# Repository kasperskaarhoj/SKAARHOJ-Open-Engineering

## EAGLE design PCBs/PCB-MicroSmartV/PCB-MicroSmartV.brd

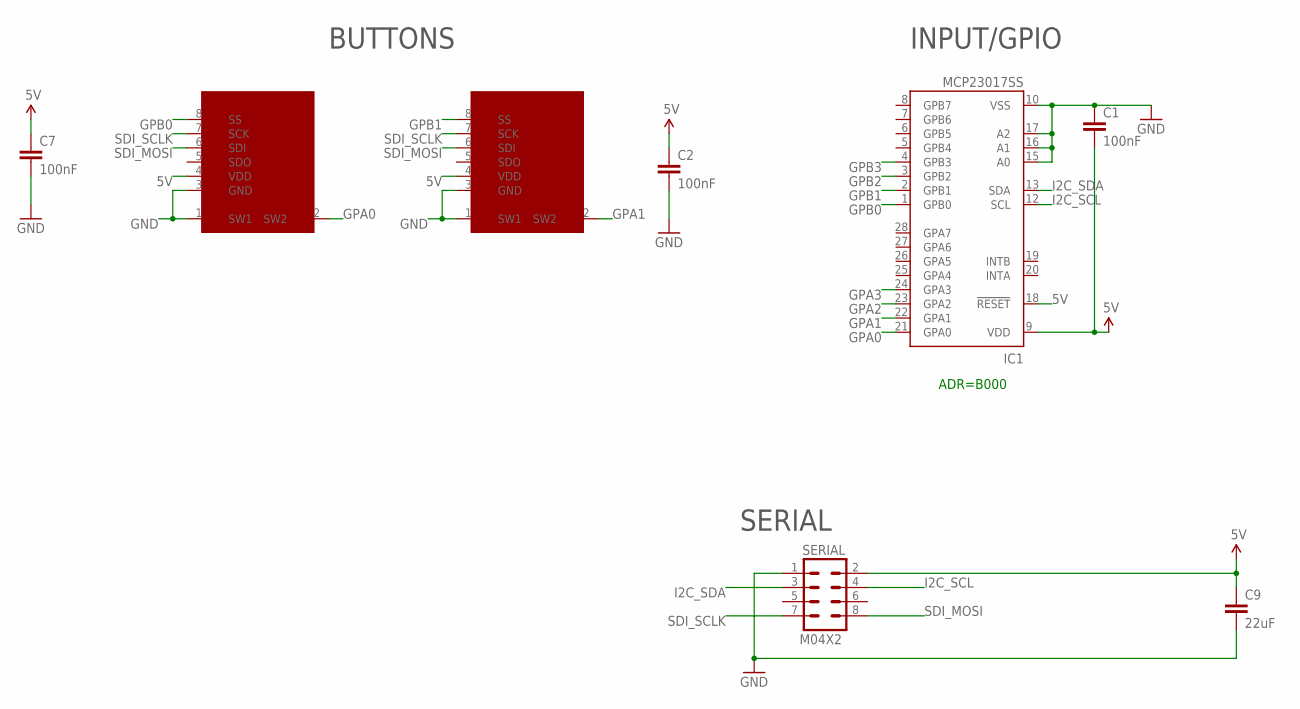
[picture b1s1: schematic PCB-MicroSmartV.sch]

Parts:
C1, C2, C7: 100nF; 0603-CAP
C9: 22uF; 0805
IC1: MCP23017SS; SSOP28; MPN MCP23017-E/SS
SERIAL: M04X2; 2X4
SSW1, SSW2: SMART_SWITCHSMART_SWITCH_8PIN; SMART_SWITCH

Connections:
5V: C1.2, C2.1, C7.1, C9.1, IC1.9 (VDD), IC1.18 (!RESET), SERIAL.2, SSW1.4 (VDD), SSW2.4 (VDD)
GND: C1.1, C2.2, C7.2, C9.2, IC1.10 (VSS), IC1.15 (A0), IC1.16 (A1), IC1.17 (A2), SERIAL.1, SSW1.1 (SW1), SSW1.3 (GND), SSW2.1 (SW1), SSW2.3 (GND)
GPA0: IC1.21 (GPA0), SSW1.2 (SW2)
GPA1: IC1.22 (GPA1), SSW2.2 (SW2)
GPA2: IC1.23 (GPA2)
GPA3: IC1.24 (GPA3)
GPB0: IC1.1 (GPB0), SSW1.8 (SS)
GPB1: IC1.2 (GPB1), SSW2.8 (SS)
GPB2: IC1.3 (GPB2)
GPB3: IC1.4 (GPB3)
I2C_SCL: IC1.12 (SCL), SERIAL.4
I2C_SDA: IC1.13 (SDA), SERIAL.3
SDI_MOSI: SERIAL.8, SSW1.6 (SDI), SSW2.6 (SDI)
SDI_SCLK: SERIAL.7, SSW1.7 (SCK), SSW2.7 (SCK)

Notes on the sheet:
ADR=B000
INPUT/GPIO
SERIAL
BUTTONS

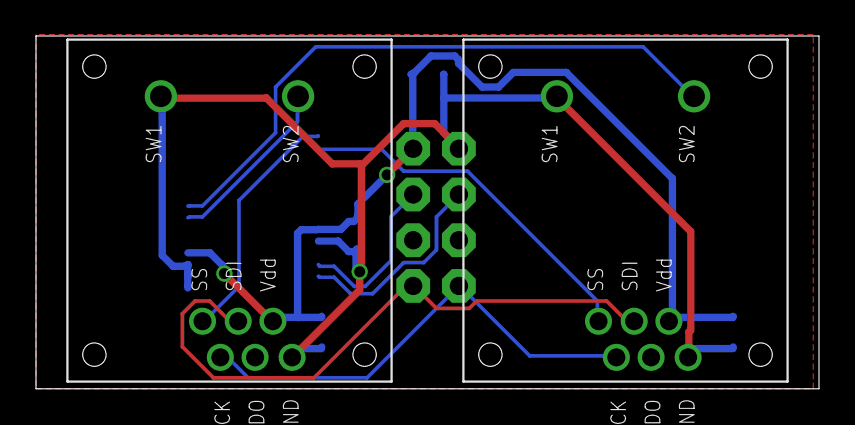
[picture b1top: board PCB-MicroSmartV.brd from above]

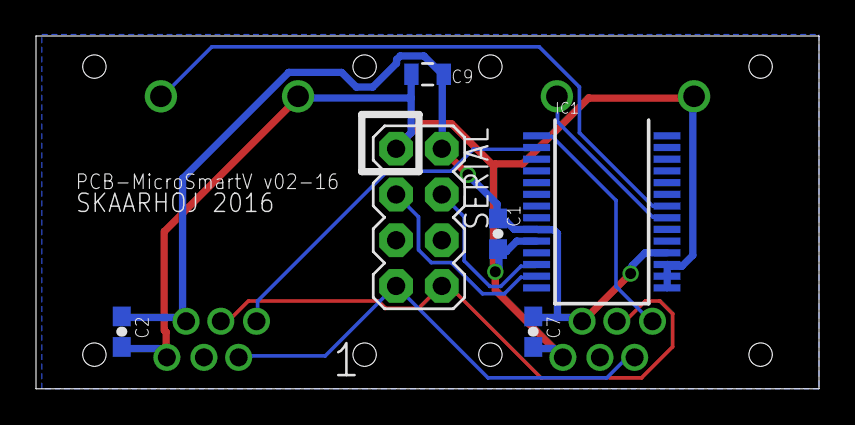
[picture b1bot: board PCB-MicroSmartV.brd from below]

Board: 2 copper layers, 43.5 x 19.6 mm, 8 parts (6 on the bottom side), 10 nets.

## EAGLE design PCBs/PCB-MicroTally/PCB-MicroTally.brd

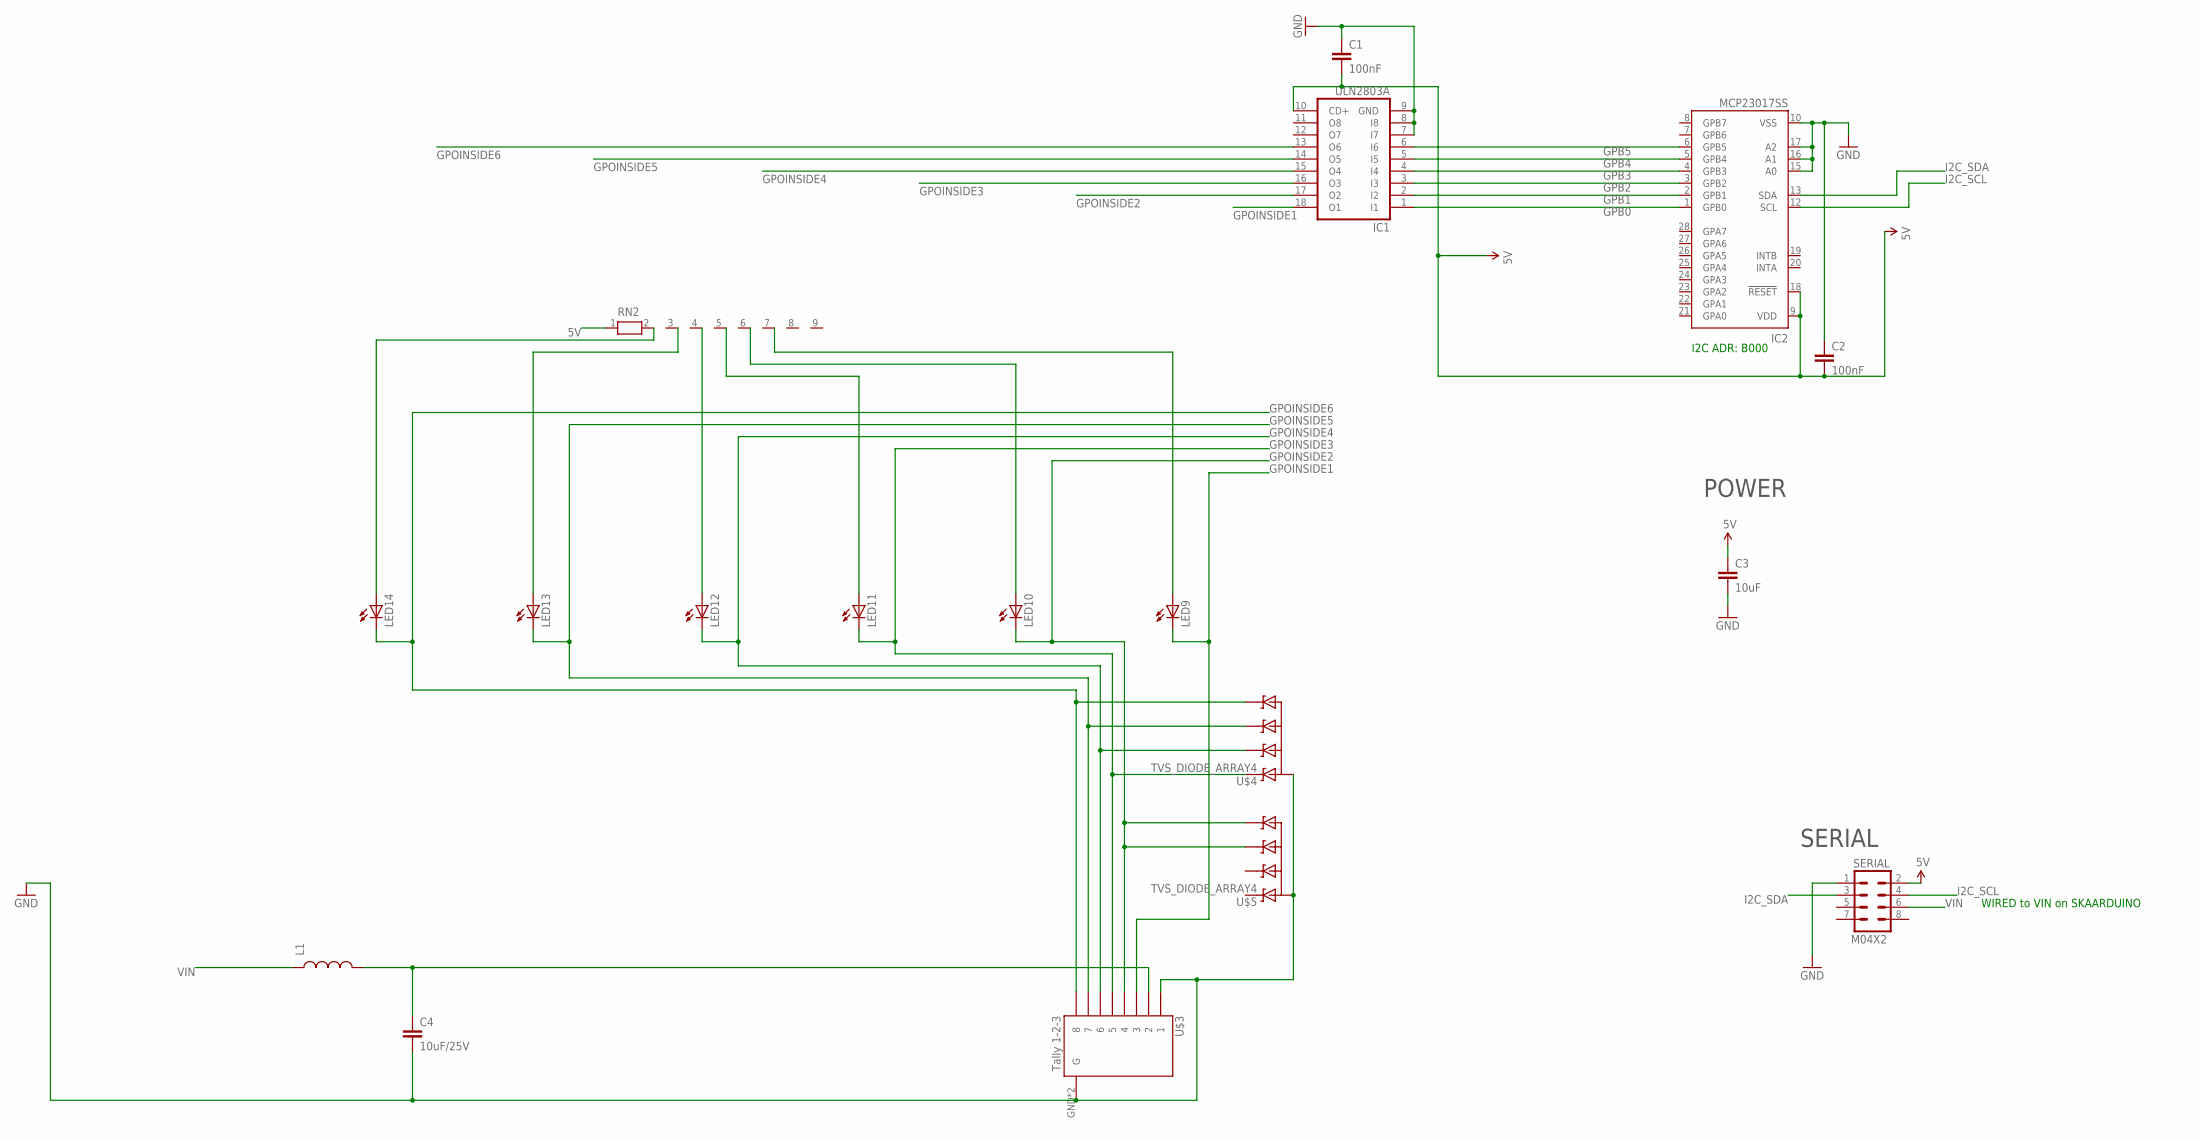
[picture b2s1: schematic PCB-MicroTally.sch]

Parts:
C1: 100nF; 0805
C2: 100nF; 0603-CAP
C3: 10uF; 0805
C4: 10uF/25V; 0805
IC1: ULN2803A; SO18W
IC2: MCP23017SS; SSOP28
L1: INDUCTOR0805; 0805
LED9, LED10, LED11, LED12, LED13, LED14: LED3MM
RN2: RN08; RN-9
SERIAL: M04X2; 2X4
U$3: Tally 1-2-3; RJ45-8_GND_UPRIGHT
U$4, U$5: TVS_DIODE_ARRAY4; SOT23-6L

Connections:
5V: C1.2, C2.2, C3.1, IC1.10 (CD+), IC2.9 (VDD), IC2.18 (!RESET), RN2.1, SERIAL.2
GND: C1.1, C2.1, C3.2, C4.2, IC1.7 (I7), IC1.8 (I8), IC1.9 (GND), IC2.10 (VSS), IC2.15 (A0), IC2.16 (A1), IC2.17 (A2), SERIAL.1, U$3.1, U$3.GND (G), U$3.GND1 (G), U$4.2 (GND), U$4.5 (GND), U$5.2 (GND), U$5.5 (GND)
GPB0: IC1.1 (I1), IC2.1 (GPB0)
GPB1: IC1.2 (I2), IC2.2 (GPB1)
GPB2: IC1.3 (I3), IC2.3 (GPB2)
GPB3: IC1.4 (I4), IC2.4 (GPB3)
GPB4: IC1.5 (I5), IC2.5 (GPB4)
GPB5: IC1.6 (I6), IC2.6 (GPB5)
GPOINSIDE1: IC1.18 (O1), LED9.K (C), U$3.3
GPOINSIDE2: IC1.17 (O2), LED10.K (C), U$3.4, U$5.4 (C), U$5.6 (D)
GPOINSIDE3: IC1.16 (O3), LED11.K (C), U$3.5, U$4.1 (A)
GPOINSIDE4: IC1.15 (O4), LED12.K (C), U$3.6, U$4.3 (B)
GPOINSIDE5: IC1.14 (O5), LED13.K (C), U$3.7, U$4.4 (C)
GPOINSIDE6: IC1.13 (O6), LED14.K (C), U$3.8, U$4.6 (D)
I2C_SCL: IC2.12 (SCL), SERIAL.4
I2C_SDA: IC2.13 (SDA), SERIAL.3
unnamed: C4.1, L1.2, U$3.2
unnamed: LED14.A, RN2.2
unnamed: LED13.A, RN2.3
unnamed: LED12.A, RN2.4
unnamed: LED11.A, RN2.5
unnamed: LED10.A, RN2.6
unnamed: LED9.A, RN2.7
VIN: L1.1, SERIAL.6

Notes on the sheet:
I2C ADR: B000
SERIAL
POWER
WIRED to VIN on SKAARDUINO

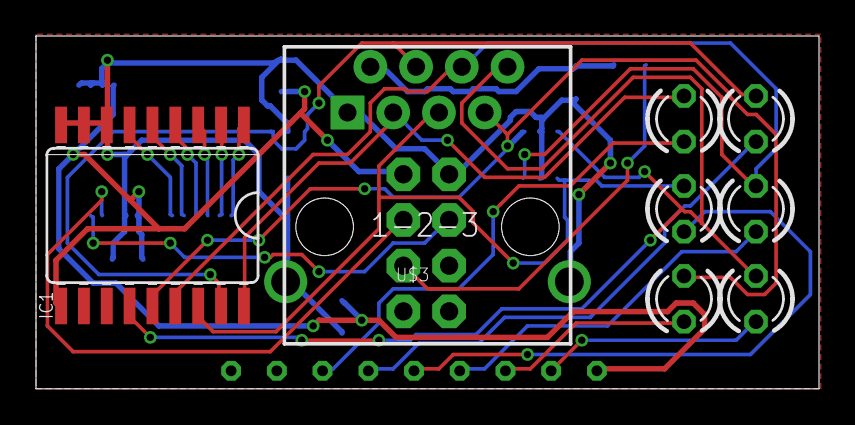
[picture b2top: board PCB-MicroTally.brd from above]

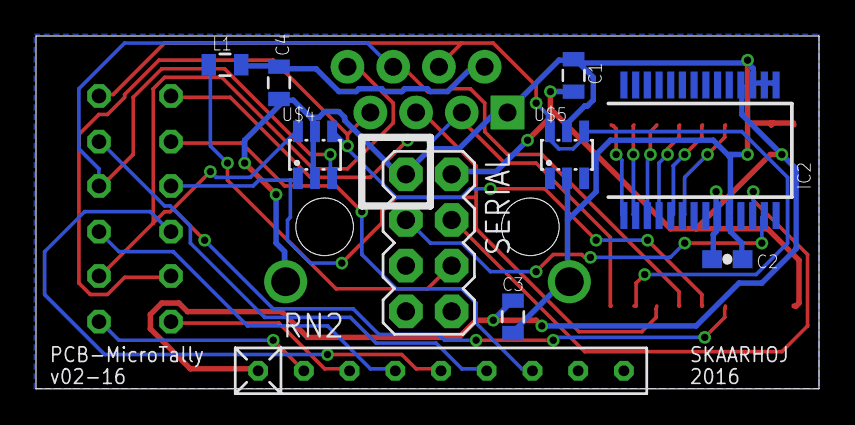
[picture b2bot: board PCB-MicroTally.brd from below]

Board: 2 copper layers, 43.5 x 19.6 mm, 18 parts (10 on the bottom side), 24 nets.

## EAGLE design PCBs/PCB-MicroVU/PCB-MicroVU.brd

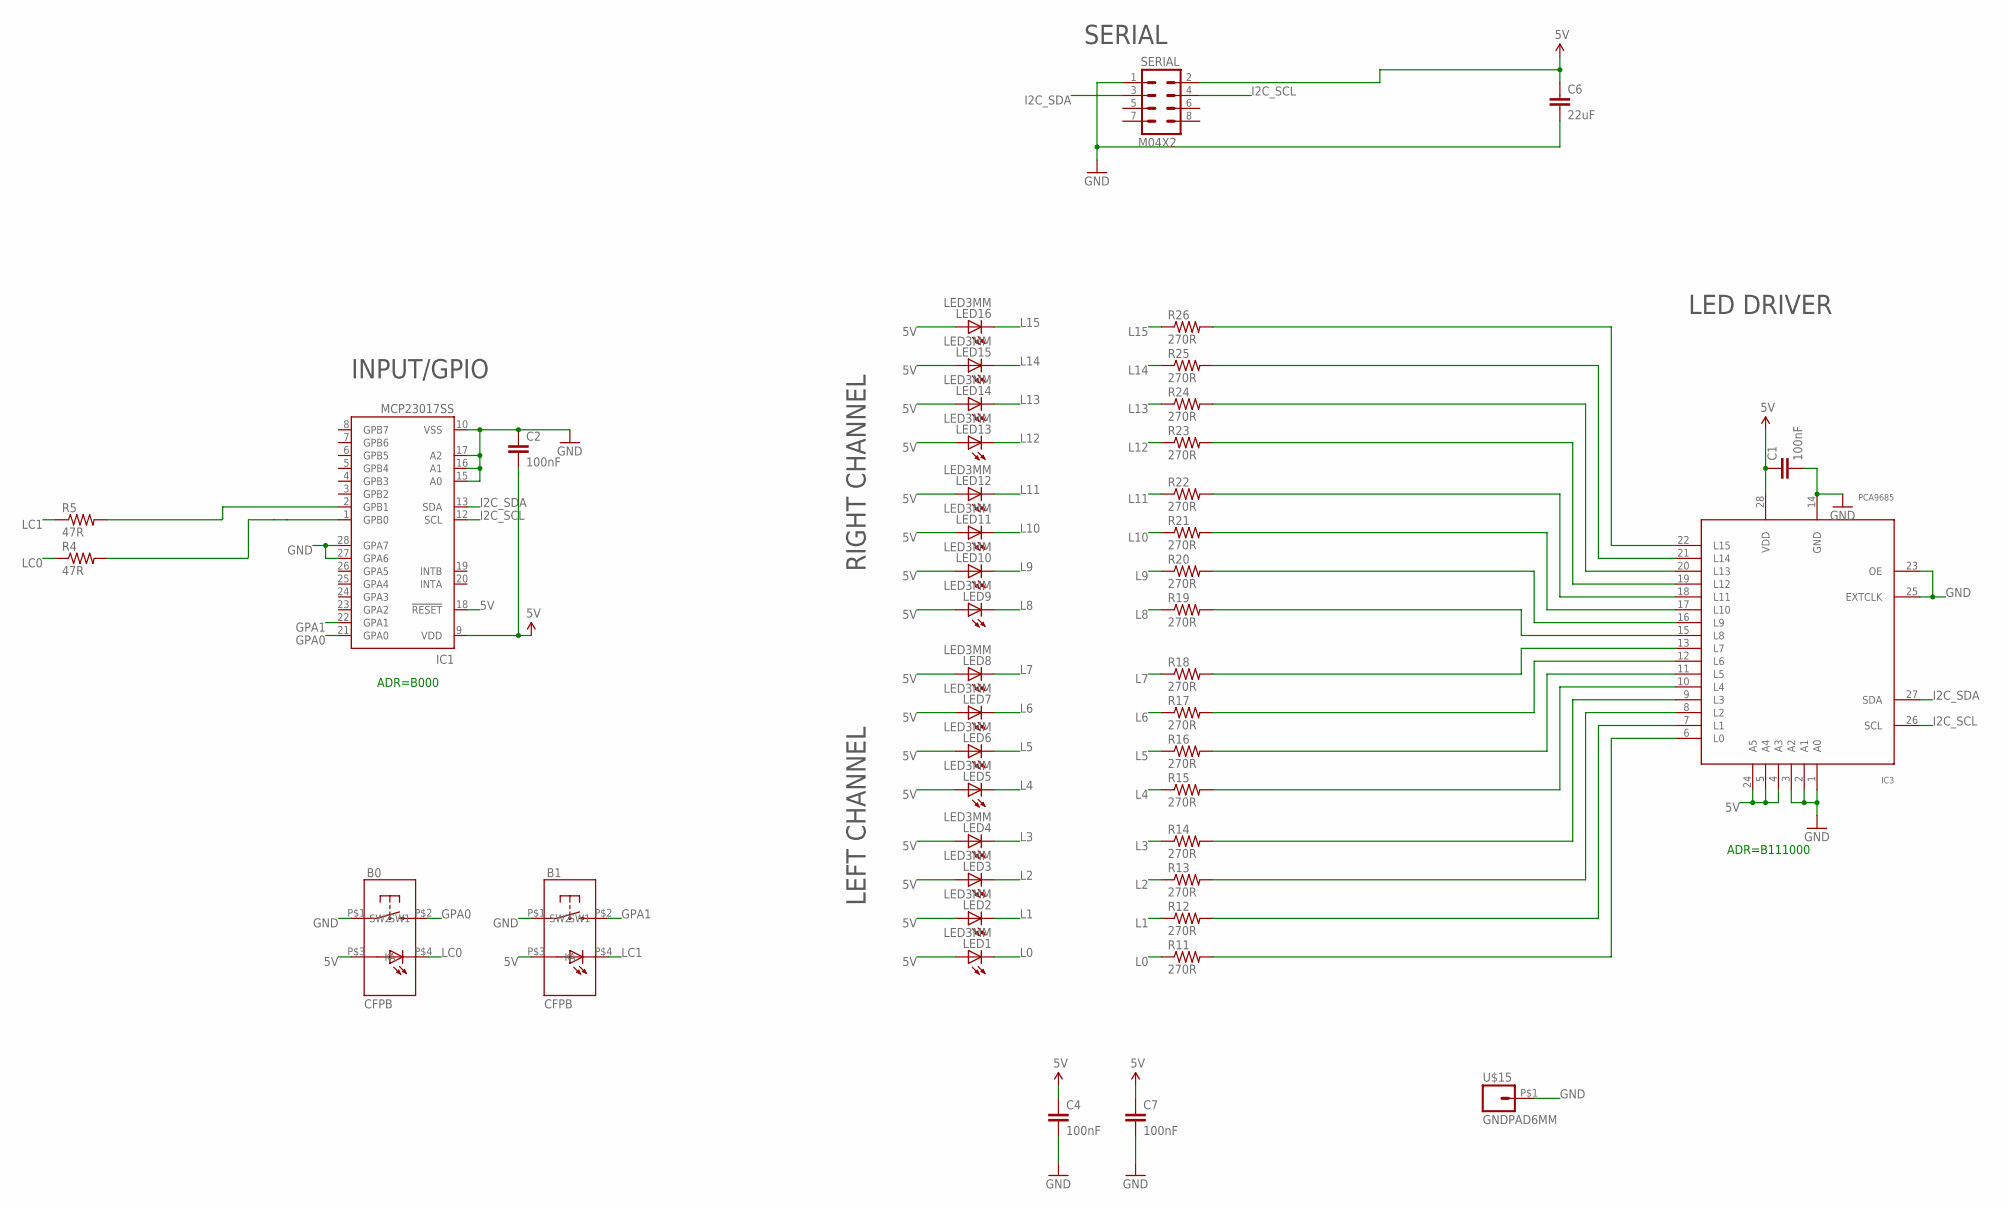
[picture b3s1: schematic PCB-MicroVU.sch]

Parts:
B0, B1: CFPB; CFPB-6/9MM
C1, C2, C4, C7: 100nF; 0603-CAP
C6: 22uF; 0805
IC1: MCP23017SS; SSOP28; MPN MCP23017-E/SS
IC3: PCA9685; TSSOP28
LED1, LED2, LED3, LED4, LED5, LED6, LED7, LED8, LED9, LED10, LED11, LED12, LED13, LED14, LED15, LED16: LED3MM
R4, R5: 47R; 0603-RES
R11, R12, R13, R14, R15, R16, R17, R18, R19, R20, R21, R22, R23, R24, R25, R26: 270R; 0603-RES
SERIAL: M04X2; 2X4
U$15: GNDPAD6MM; 3.2MMPAD6MM

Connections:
5V: B0.P$3 (A), B1.P$3 (A), C1.1, C2.2, C4.1, C6.1, C7.1, IC1.9 (VDD), IC1.18 (!RESET), IC3.4 (A3), IC3.5 (A4), IC3.24 (A5), IC3.28 (VDD), LED1.A, LED2.A, LED3.A, LED4.A, LED5.A, LED6.A, LED7.A, LED8.A, LED9.A, LED10.A, LED11.A, LED12.A, LED13.A, LED14.A, LED15.A, LED16.A, SERIAL.2
GND: B0.P$1 (SW1), B1.P$1 (SW1), C1.2, C2.1, C4.2, C6.2, C7.2, IC1.10 (VSS), IC1.15 (A0), IC1.16 (A1), IC1.17 (A2), IC1.27 (GPA6), IC1.28 (GPA7), IC3.1 (A0), IC3.2 (A1), IC3.3 (A2), IC3.14 (GND), IC3.23 (OE), IC3.25 (EXTCLK), SERIAL.1, U$15.P$1
GPA0: B0.P$2 (SW2), IC1.21 (GPA0)
GPA1: B1.P$2 (SW2), IC1.22 (GPA1)
I2C_SCL: IC1.12 (SCL), IC3.26 (SCL), SERIAL.4
I2C_SDA: IC1.13 (SDA), IC3.27 (SDA), SERIAL.3
L0: LED1.K (C), R11.1
L1: LED2.K (C), R12.1
L2: LED3.K (C), R13.1
L3: LED4.K (C), R14.1
L4: LED5.K (C), R15.1
L5: LED6.K (C), R16.1
L6: LED7.K (C), R17.1
L7: LED8.K (C), R18.1
L8: LED9.K (C), R19.1
L9: LED10.K (C), R20.1
L10: LED11.K (C), R21.1
L11: LED12.K (C), R22.1
L12: LED13.K (C), R23.1
L13: LED14.K (C), R24.1
L14: LED15.K (C), R25.1
L15: LED16.K (C), R26.1
LC0: B0.P$4 (K), R4.1
LC1: B1.P$4 (K), R5.1
unnamed: IC1.2 (GPB1), R5.2
unnamed: IC1.1 (GPB0), R4.2
unnamed: IC3.6 (L0), R11.2
unnamed: IC3.19 (L12), R23.2
unnamed: IC3.21 (L14), R25.2
unnamed: IC3.13 (L7), R18.2
unnamed: IC3.12 (L6), R17.2
unnamed: IC3.11 (L5), R16.2
unnamed: IC3.10 (L4), R15.2
unnamed: IC3.9 (L3), R14.2
unnamed: IC3.8 (L2), R13.2
unnamed: IC3.7 (L1), R12.2
unnamed: IC3.15 (L8), R19.2
unnamed: IC3.16 (L9), R20.2
unnamed: IC3.17 (L10), R21.2
unnamed: IC3.18 (L11), R22.2
unnamed: IC3.20 (L13), R24.2
unnamed: IC3.22 (L15), R26.2

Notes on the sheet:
LEFT CHANNEL
RIGHT CHANNEL
SERIAL
ADR=B000
INPUT/GPIO
ADR=B111000
LED DRIVER

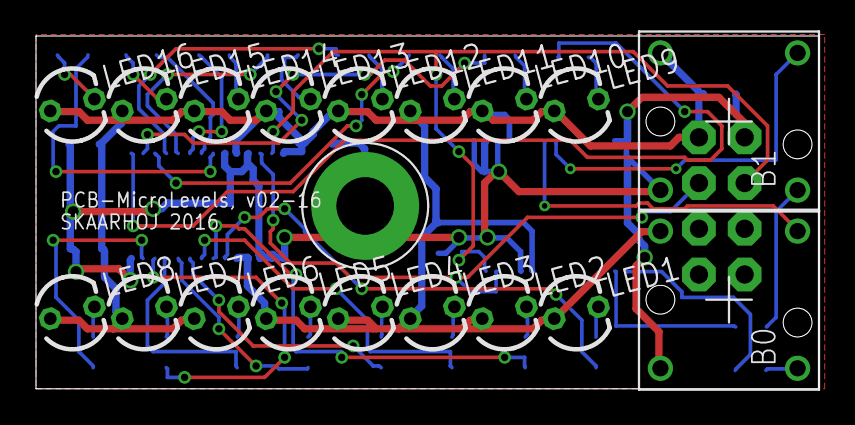
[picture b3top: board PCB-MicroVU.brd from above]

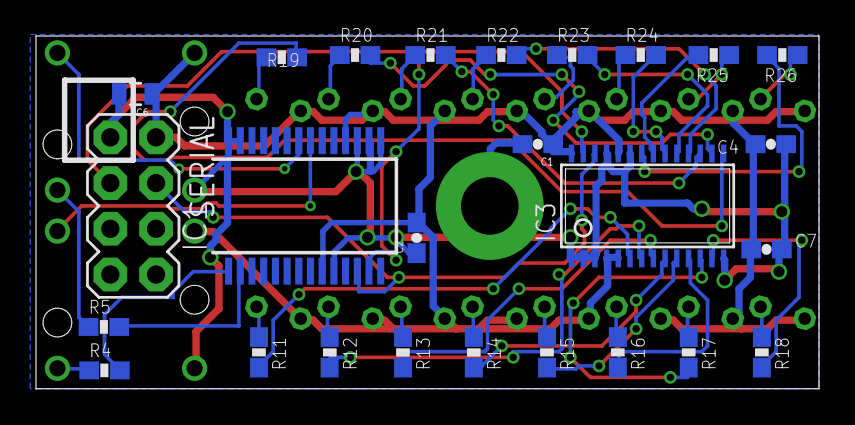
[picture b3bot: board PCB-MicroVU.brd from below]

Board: 2 copper layers, 43.5 x 19.6 mm, 45 parts (26 on the bottom side), 42 nets.

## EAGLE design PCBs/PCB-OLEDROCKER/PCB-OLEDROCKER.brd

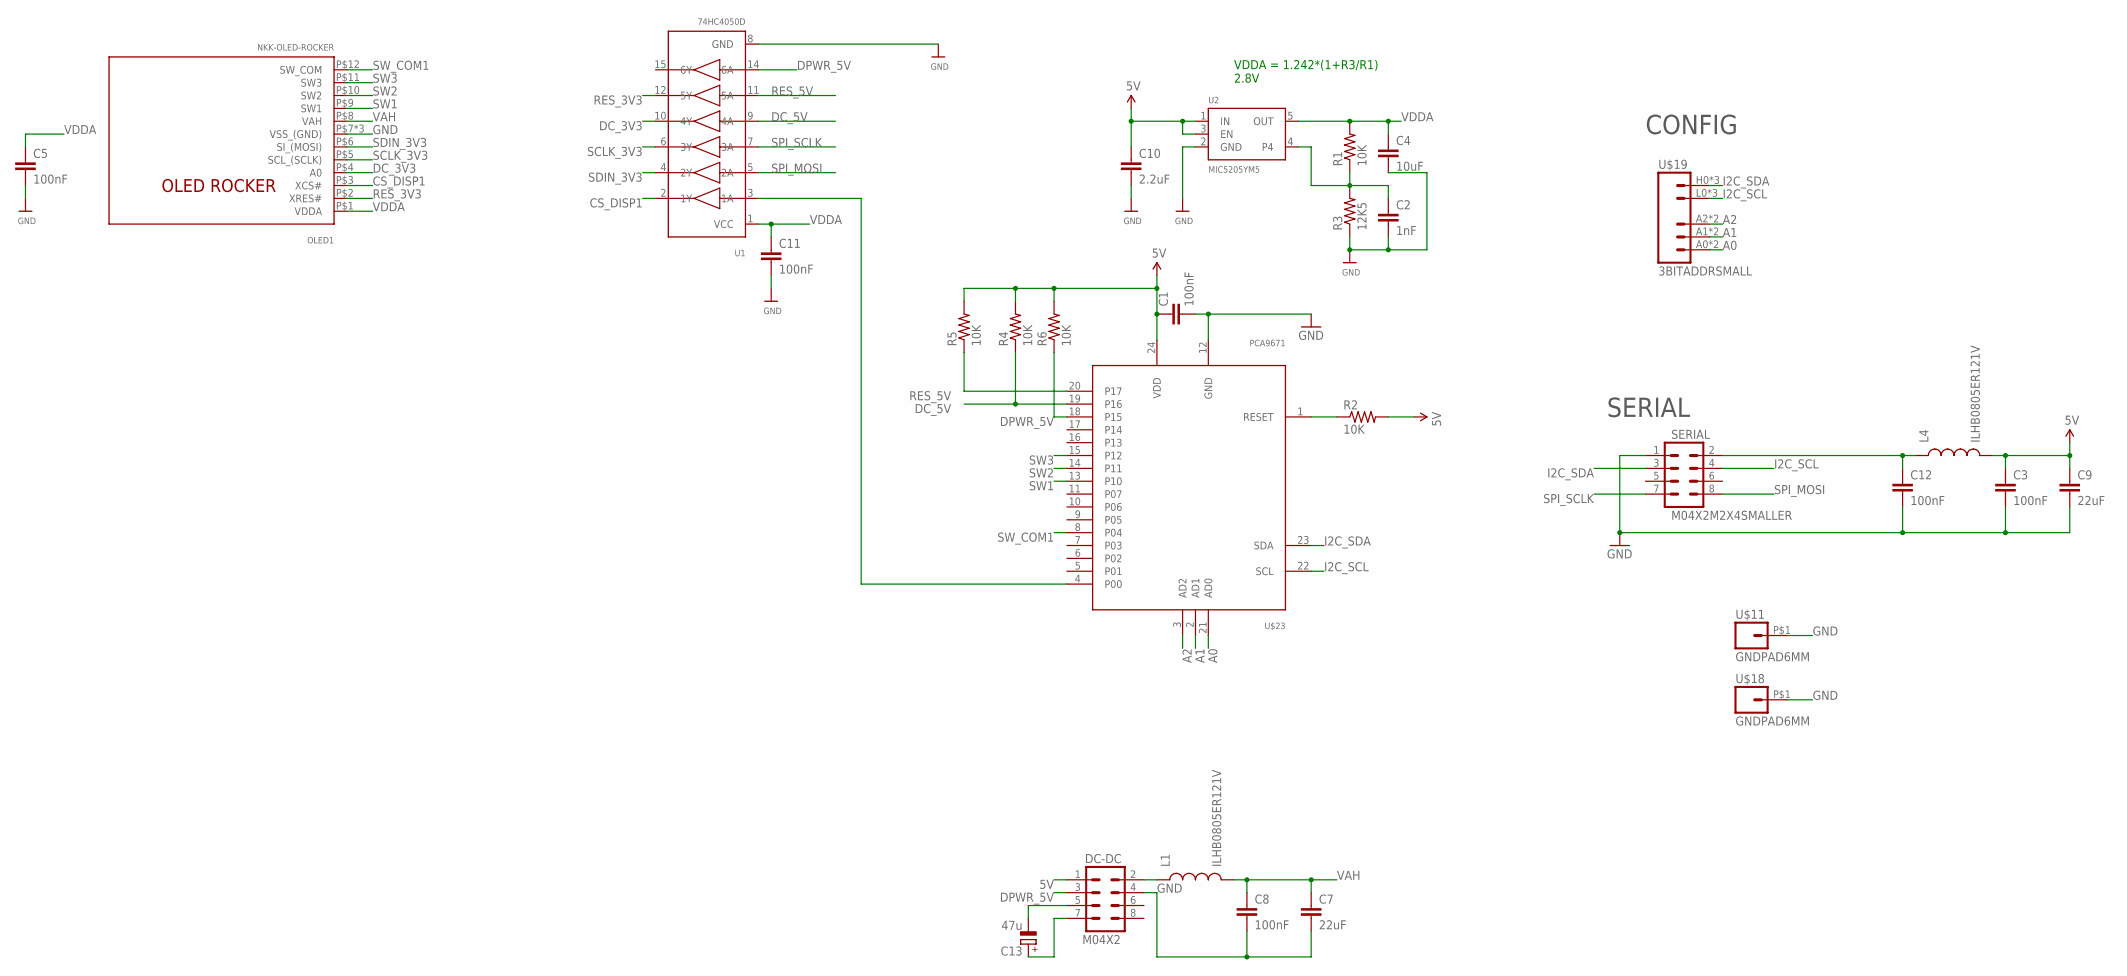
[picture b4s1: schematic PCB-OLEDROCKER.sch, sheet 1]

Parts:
C1, C3, C5, C8, C11, C12: 100nF; 0603-CAP
C2: 1nF; 0603-CAP
C4: 10uF; 0805
C7, C9: 22uF; 0805
C10: 2.2uF; 0603-CAP
C13: 47u; PANASONIC_D
DC-DC: M04X2; 2X4
L1, L4: ILHB0805ER121V; 0805
OLED1: NKK-OLED-ROCKER; JST_BM12B-SURS
R1, R2, R4, R5, R6: 10K; 0603-RES
R3: 12K5; 0603-RES
SERIAL: M04X2M2X4SMALLER; M2X4SMALLER
U1: 74HC4050D; TSSOP16
U2: MIC5205YM5; SOT23-5
U$11, U$18: GNDPAD6MM; 3.2MMPAD6MM
U$19: 3BITADDRSMALL; 3BITADDR_SMALL
U$23: PCA9671; TSSOP24

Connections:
5V: C1.1, C3.1, C9.1, C10.1, DC-DC.1, L4.2, R2.2, R4.2, R5.2, R6.2, U2.1 (IN), U2.3 (EN), U$23.24 (VDD)
A0: U$19.A0, U$19.AS0 (A0), U$23.21 (AD0)
A1: U$19.A1, U$19.AS1 (A1), U$23.2 (AD1)
A2: U$19.A2, U$19.AS2 (A2), U$23.3 (AD2)
ARD_5V: C12.1, L4.1, SERIAL.2
ARD_5V1: DC-DC.2, L1.1
CS_DISP1: OLED1.P$3 (XCS#), U1.2 (1Y)
DC_3V3: OLED1.P$4 (A0), U1.10 (4Y)
DC_5V: R4.1, U1.9 (4A), U$23.19 (P16)
DPWR_5V: DC-DC.3, R6.1, U1.14 (6A), U$23.18 (P15)
GND: C1.2, C2.2, C3.2, C4.2, C5.2, C7.2, C8.2, C9.2, C10.2, C11.2, C12.2, DC-DC.4, OLED1.P$7 (VSS_(GND)), OLED1.SUPPORT1 (VSS_(GND)), OLED1.SUPPORT2 (VSS_(GND)), R3.1, SERIAL.1, U1.8 (GND), U2.2 (GND), U$11.P$1, U$18.P$1, U$23.12 (GND)
I2C_SCL: SERIAL.4, U$19.L0 (GND), U$19.L1 (GND), U$19.L2 (GND), U$23.22 (SCL)
I2C_SDA: SERIAL.3, U$19.H0 (VCC), U$19.H1 (VCC), U$19.H2 (VCC), U$23.23 (SDA)
unnamed: R2.1, U$23.1 (RESET)
unnamed: C13.-, DC-DC.5
unnamed: C2.1, R1.1, R3.2, U2.4
unnamed: C13.+, DC-DC.7
unnamed: U1.3 (1A), U$23.4 (P00)
RES_3V3: OLED1.P$2 (XRES#), U1.12 (5Y)
RES_5V: R5.1, U1.11 (5A), U$23.20 (P17)
SCLK_3V3: OLED1.P$5 (SCL_(SCLK)), U1.6 (3Y)
SDIN_3V3: OLED1.P$6 (SI_(MOSI)), U1.4 (2Y)
SPI_MOSI: SERIAL.8, U1.5 (2A)
SPI_SCLK: SERIAL.7, U1.7 (3A)
SW1: OLED1.P$9 (SW1), U$23.13 (P10)
SW2: OLED1.P$10 (SW2), U$23.14 (P11)
SW3: OLED1.P$11 (SW3), U$23.15 (P12)
SW_COM1: OLED1.P$12 (SW_COM), U$23.8 (P04)
VAH: C7.1, C8.1, L1.2, OLED1.P$8 (VAH)
VDDA: C4.1, C5.1, C11.1, OLED1.P$1 (VDDA), R1.2, U1.1 (VCC), U2.5 (OUT)

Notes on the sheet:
SERIAL
CONFIG
VDDA = 1.242*(1+R3/R1) 2.8V

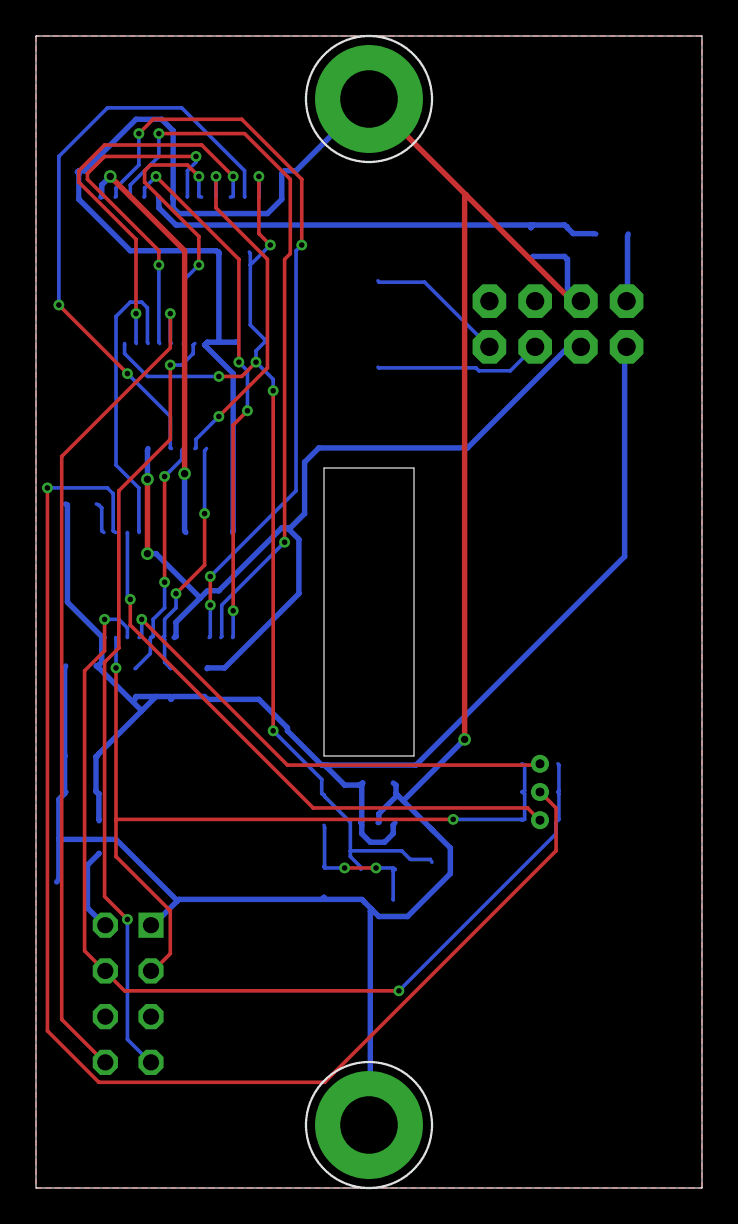
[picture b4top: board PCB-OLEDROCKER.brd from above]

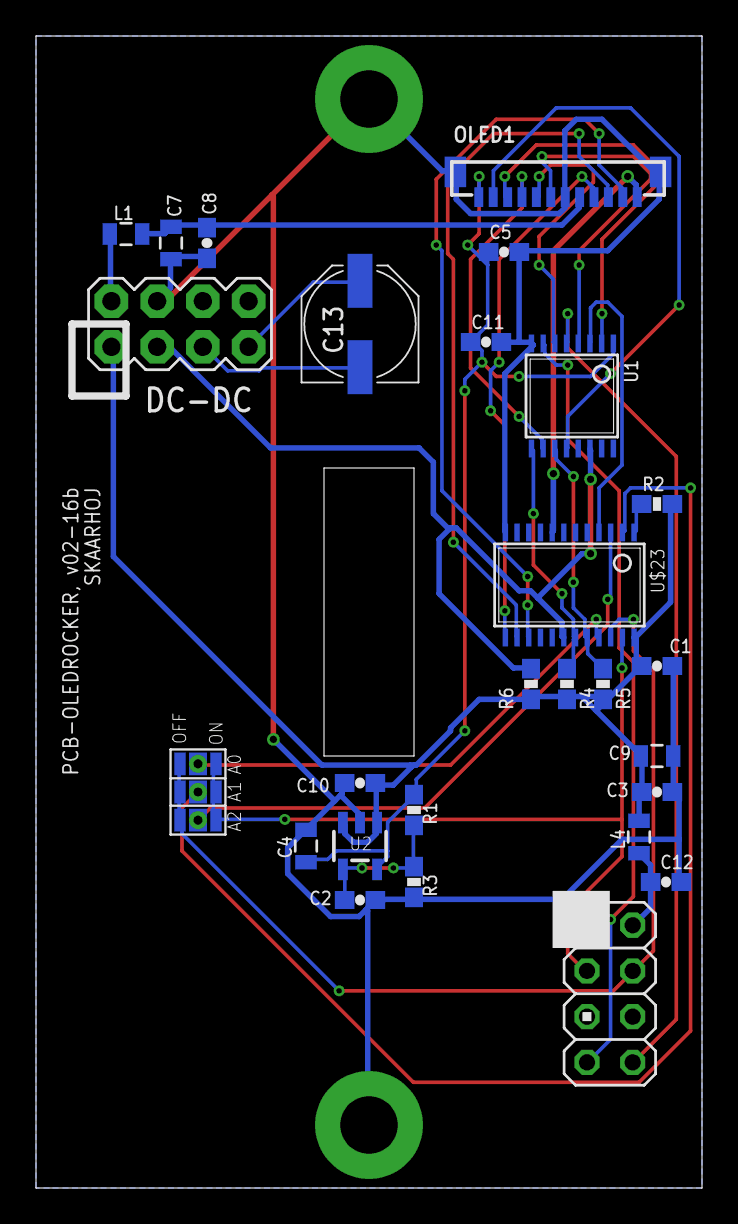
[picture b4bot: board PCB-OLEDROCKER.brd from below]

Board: 2 copper layers, 37.0 x 64.0 mm, 29 parts (27 on the bottom side), 30 nets.

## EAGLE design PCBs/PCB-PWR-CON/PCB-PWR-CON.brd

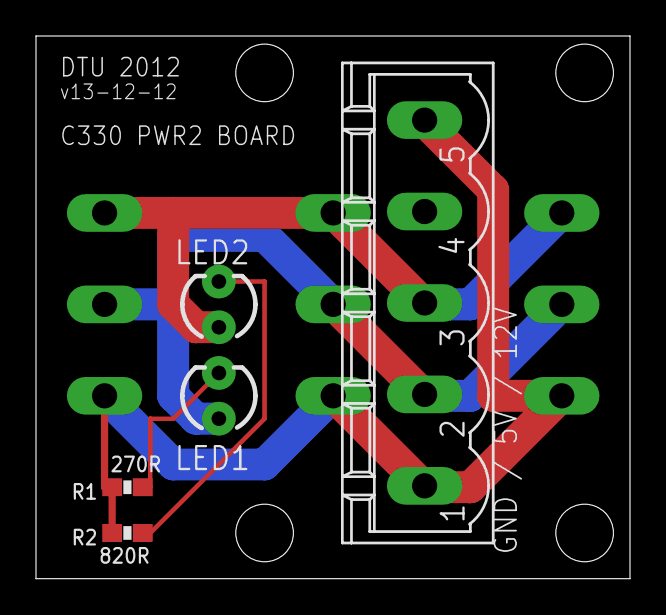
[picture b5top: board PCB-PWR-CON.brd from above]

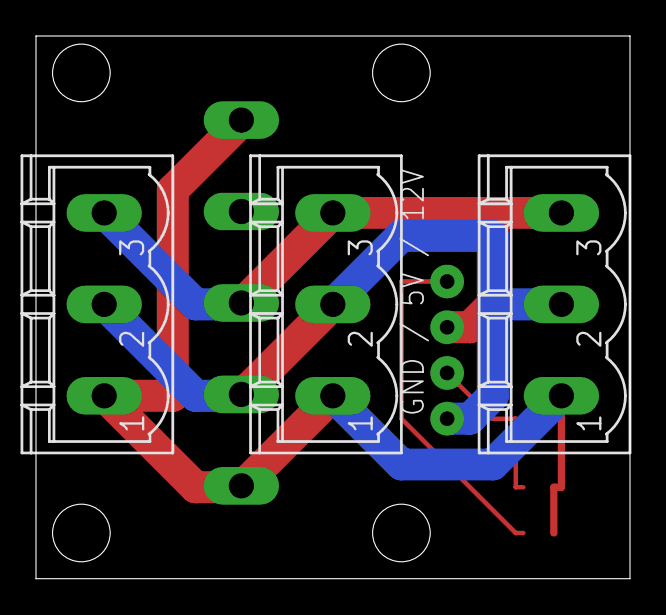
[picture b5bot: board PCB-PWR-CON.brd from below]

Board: 2 copper layers, 33.0 x 30.1 mm, 8 parts (3 on the bottom side), 5 nets.

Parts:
LED1, LED2: LED3MM
OUT2, OUT3, OUT4: CON1; MSTBV3
R1: 270R; 0603-RES
R2: 820R; 0603-RES
X2: MSTBV5

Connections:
5V: LED1.A, OUT2.2, OUT3.2, OUT4.2, X2.2
12V: LED2.A, OUT2.3, OUT3.3, OUT4.3, X2.3
GND: OUT2.1, OUT3.1, OUT4.1, R1.1, R2.1, X2.1, X2.5
unnamed: LED1.K, R1.2
unnamed: LED2.K, R2.2

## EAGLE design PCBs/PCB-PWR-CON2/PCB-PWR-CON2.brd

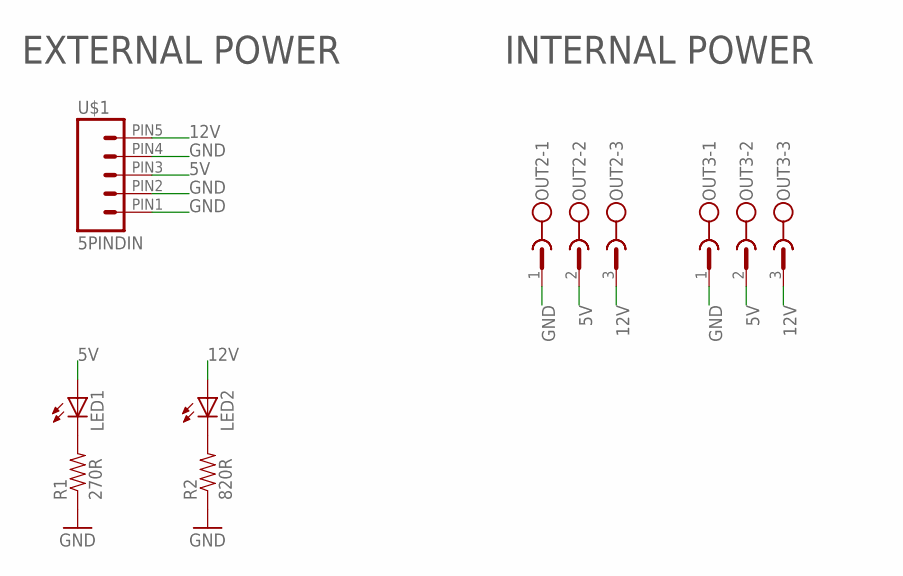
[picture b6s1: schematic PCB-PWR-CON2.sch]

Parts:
LED1, LED2: LED3MM
OUT2, OUT3: CON1; MSTBV3
R1: 270R; 0603-RES
R2: 820R; 0603-RES
U$1: 5PINDIN

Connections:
5V: LED1.A, OUT2.2, OUT3.2, U$1.PIN3 (3)
12V: LED2.A, OUT2.3, OUT3.3, U$1.PIN5 (5)
GND: OUT2.1, OUT3.1, R1.1, R2.1, U$1.PIN1 (1), U$1.PIN2 (2), U$1.PIN4 (4)
unnamed: LED1.K (C), R1.2
unnamed: LED2.K (C), R2.2

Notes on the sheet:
INTERNAL POWER
EXTERNAL POWER

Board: 2 copper layers, 7 parts (2 on the bottom side), 5 nets, no tracks yet.

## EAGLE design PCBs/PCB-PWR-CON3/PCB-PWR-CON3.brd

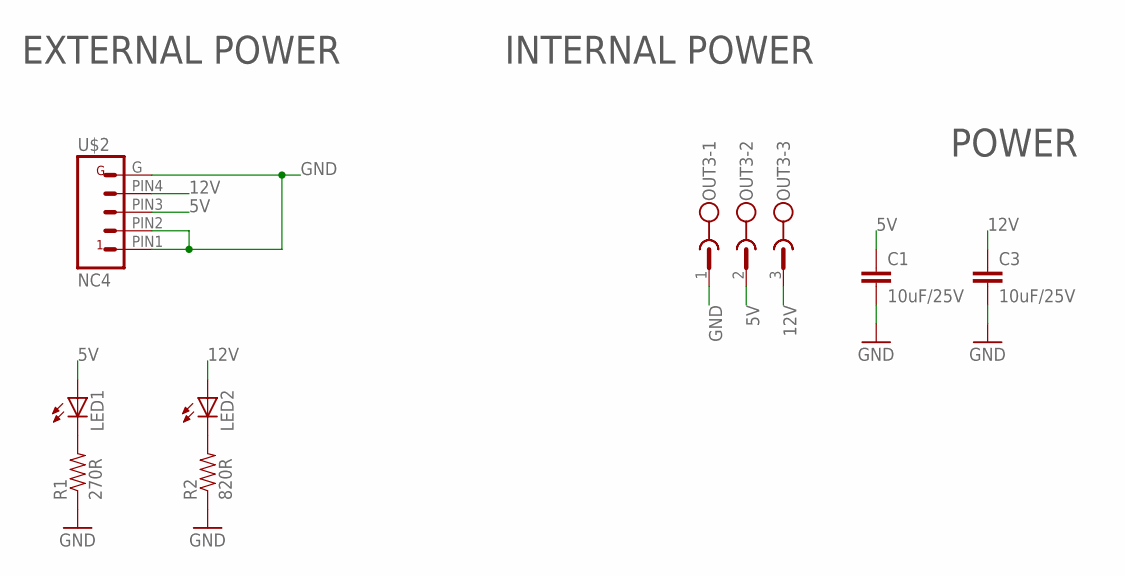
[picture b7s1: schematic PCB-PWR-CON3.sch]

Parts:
C1, C3: 10uF/25V; 0805
LED1, LED2: LED3MM
OUT3: CON1; MSTBV3
R1: 270R; 0603-RES
R2: 820R; 0603-RES
U$2: NC4; NC4-MD-L1

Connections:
5V: C1.1, LED1.A, OUT3.2, U$2.PIN3 (3)
12V: C3.1, LED2.A, OUT3.3, U$2.PIN4 (4)
GND: C1.2, C3.2, OUT3.1, R1.1, R2.1, U$2.G, U$2.PIN1 (1), U$2.PIN2 (2)
unnamed: LED1.K (C), R1.2
unnamed: LED2.K (C), R2.2

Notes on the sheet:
POWER
INTERNAL POWER
EXTERNAL POWER

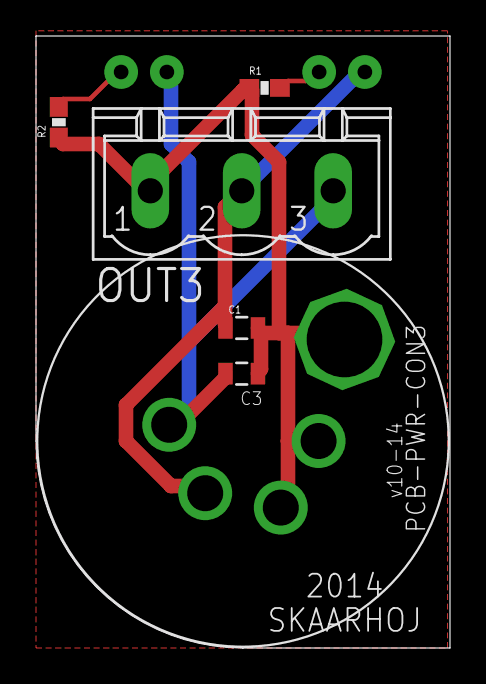
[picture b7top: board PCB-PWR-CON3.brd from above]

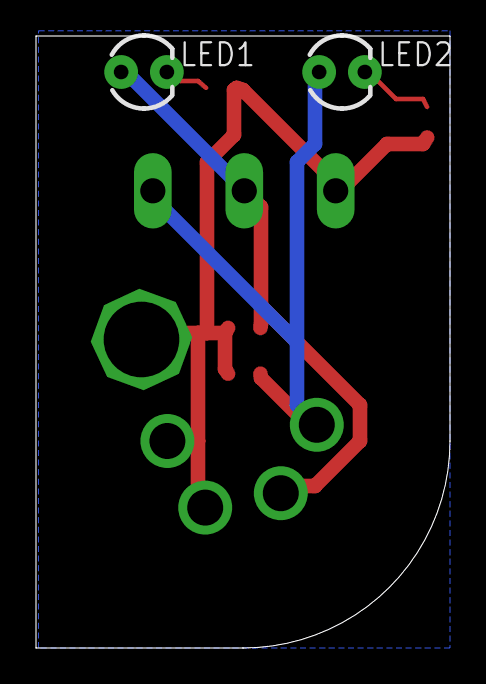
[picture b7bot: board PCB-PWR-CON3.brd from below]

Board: 2 copper layers, 23.0 x 34.0 mm, 8 parts (2 on the bottom side), 5 nets.

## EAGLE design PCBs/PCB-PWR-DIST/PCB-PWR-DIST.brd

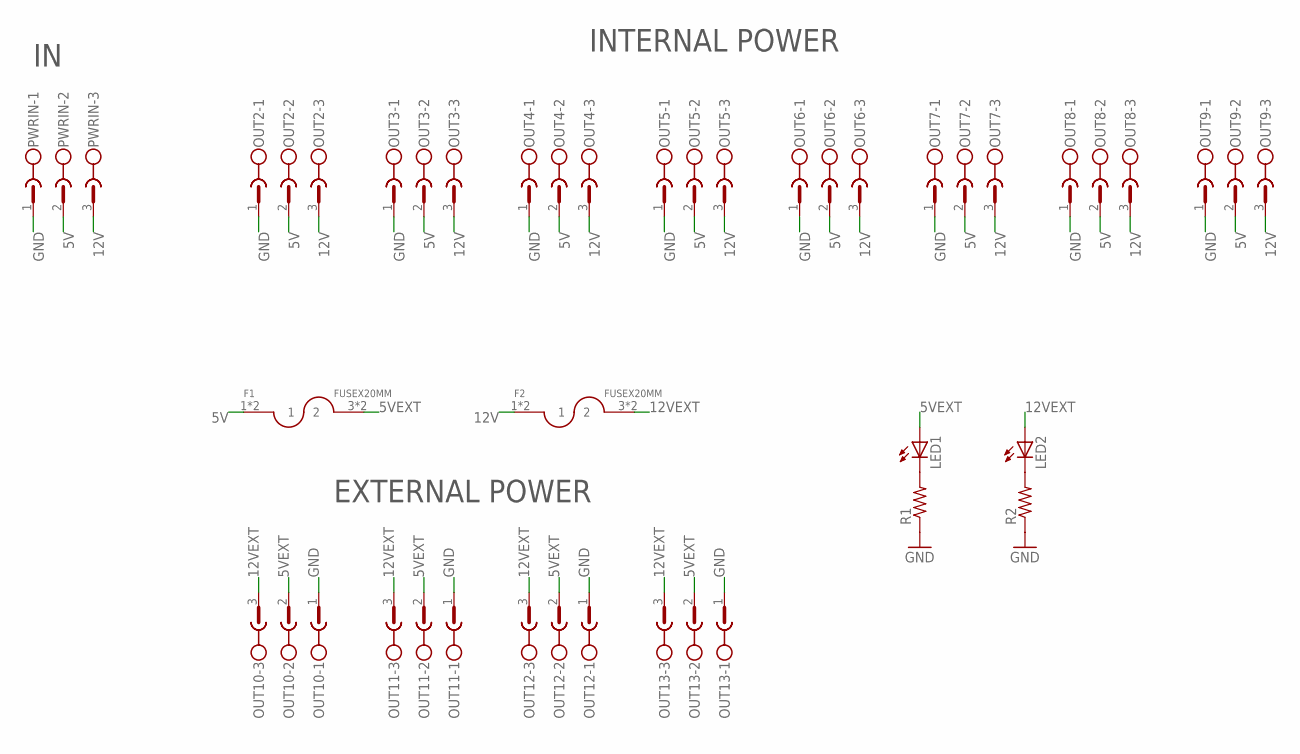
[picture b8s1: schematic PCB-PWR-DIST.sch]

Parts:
F1, F2: FUSEX20MM; FUSE_5MM
LED1, LED2: LED3MM
OUT2, OUT3, OUT4, OUT5, OUT6, OUT7, OUT8, OUT9, OUT10, OUT11, OUT12, OUT13: CON1; MSTBV3
PWRIN: CON1; MSTBV3
R1, R2: RESISTORPTH-1/4W; AXIAL-0.4

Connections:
5V: F1.1, F1.2 (1), OUT2.2, OUT3.2, OUT4.2, OUT5.2, OUT6.2, OUT7.2, OUT8.2, OUT9.2, PWRIN.2
5VEXT: F1.3 (2), F1.4 (2), LED1.A, OUT10.2, OUT11.2, OUT12.2, OUT13.2
12V: F2.1, F2.2 (1), OUT2.3, OUT3.3, OUT4.3, OUT5.3, OUT6.3, OUT7.3, OUT8.3, OUT9.3, PWRIN.3
12VEXT: F2.3 (2), F2.4 (2), LED2.A, OUT10.3, OUT11.3, OUT12.3, OUT13.3
GND: OUT2.1, OUT3.1, OUT4.1, OUT5.1, OUT6.1, OUT7.1, OUT8.1, OUT9.1, OUT10.1, OUT11.1, OUT12.1, OUT13.1, PWRIN.1, R1.P$1 (1), R2.P$1 (1)
unnamed: LED1.K (C), R1.P$2 (2)
unnamed: LED2.K (C), R2.P$2 (2)

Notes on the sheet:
INTERNAL POWER
EXTERNAL POWER

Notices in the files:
parts and their libraries:
SparkFun: Licensing: CC v3.0 Share-Alike You are welcome to use this library for commercial purposes.
